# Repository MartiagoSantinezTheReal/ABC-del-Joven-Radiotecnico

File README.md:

# ABC-del-Joven-Radiotecnico
Este repositorio contendrá todos mis avances mientras leo el libro "ABC del Joven Radiotécnico" de Viktor Borísov, con el objetivo final de implementar la Radio Superheterodína que se muestra en el libro para el curso EL3202 "Circuitos Eléctricos Analógicos". Este repositorio posteriormente será utilizado para continuar adaptando el libro.

El objetivo primario de este repositorio, como se mencionó anteriormente, será el estudio del libro, particularmente desde la Charla 11 en adelante, sin embargo esto cambiará cuando termine el curso, ya que tengo la intención de hacer un análisis y adaptación del libro completo para que utilice componentes modernos (El libro fue escrito en los 80s en la Union Sovietica por lo que los componentes en los que se basan los circuitos son, al menos, dificiles de conseguir). 

Digo lo anterior ya que me saltaré partes del libro como la elaboración de fuentes de poder o condensadores variables ya que en el laboratorio tendré acceso a estas piezas (Como dije anteriormente es un tema al que volveré en un futuro). 

Tengo también la intención de traducir ediciones de la revista sovietica “Radio” ya que esta tiene una gran cantidad de información util para radioaficionados y sus circuitos deben pasar por un proceso similar al de los circuitos del libro para que puedan ser usados actualmente. Sin embargo esto será trabajo futuro y solo será si consigo permiso del dueño de la página de la cual estoy obteniendo las revistas para hacer este trabajo.

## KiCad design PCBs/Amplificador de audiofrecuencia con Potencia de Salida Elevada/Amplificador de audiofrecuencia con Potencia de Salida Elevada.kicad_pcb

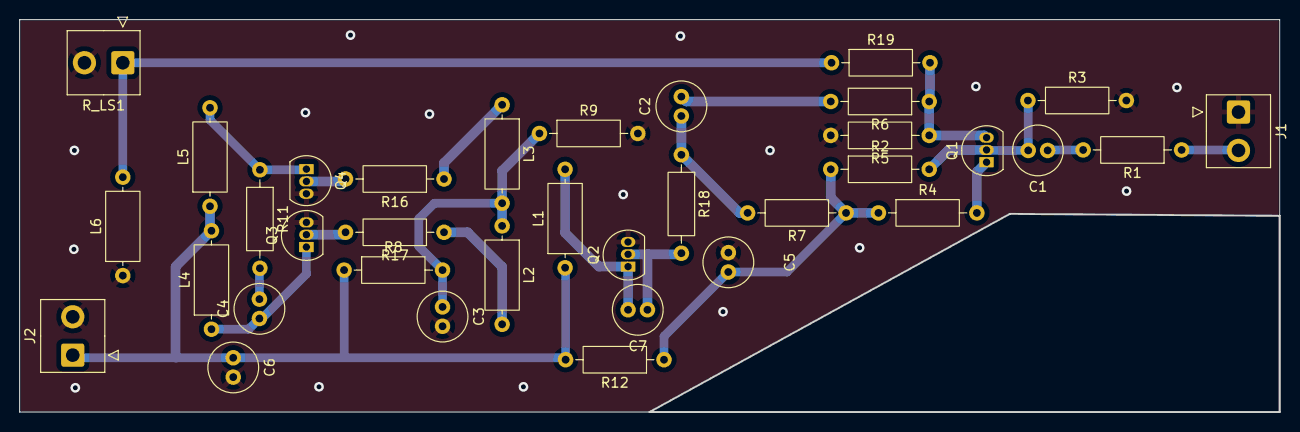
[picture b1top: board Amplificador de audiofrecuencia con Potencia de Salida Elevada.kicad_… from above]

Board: 2 copper layers, 130.0 x 40.4 mm, 35 parts (0 on the bottom side), 21 nets.

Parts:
C1: 1u; C_Radial_D5.0mm_H11.0mm_P2.00mm
C2: 10u; C_Radial_D5.0mm_H11.0mm_P2.00mm
C3: 100u; C_Radial_D5.0mm_H11.0mm_P2.00mm
C4: 0.01u; C_Radial_D5.0mm_H11.0mm_P2.00mm
C5: c=25u; C_Radial_D5.0mm_H11.0mm_P2.00mm
C6: 470u; C_Radial_D5.0mm_H11.0mm_P2.00mm
C7: 1n; C_Radial_D5.0mm_H11.0mm_P2.00mm
J1, J2: Conn_01x02_Socket; TE_826576-2_1x02_P3.96mm_Vertical
L1: 100m; L_Axial_L7.0mm_D3.3mm_P10.16mm_Horizontal_Fastron_MICC
L2, L3: 13.9m; L_Axial_L7.0mm_D3.3mm_P10.16mm_Horizontal_Fastron_MICC
L4, L5: 160m; L_Axial_L7.0mm_D3.3mm_P10.16mm_Horizontal_Fastron_MICC
L6: 10m; L_Axial_L7.0mm_D3.3mm_P10.16mm_Horizontal_Fastron_MICC
Q1, Q2: 2N3906; TO-92L_Inline
Q3, Q4: BC327-40; TO-92L_Inline
R1, R6, R12: r=1k; R_Axial_DIN0207_L6.3mm_D2.5mm_P10.16mm_Horizontal
R2: 820k; R_Axial_DIN0207_L6.3mm_D2.5mm_P10.16mm_Horizontal
R3: 1G; R_Axial_DIN0207_L6.3mm_D2.5mm_P10.16mm_Horizontal
R4, R5: 4.7k; R_Axial_DIN0207_L6.3mm_D2.5mm_P10.16mm_Horizontal
R7: 82k; R_Axial_DIN0207_L6.3mm_D2.5mm_P10.16mm_Horizontal
R8: 3.1k; R_Axial_DIN0207_L6.3mm_D2.5mm_P10.16mm_Horizontal
R9: 270; R_Axial_DIN0207_L6.3mm_D2.5mm_P10.16mm_Horizontal
R11, R16, R17: 100; R_Axial_DIN0207_L6.3mm_D2.5mm_P10.16mm_Horizontal
R18: 47; R_Axial_DIN0207_L6.3mm_D2.5mm_P10.16mm_Horizontal
R19: 22k; R_Axial_DIN0207_L6.3mm_D2.5mm_P10.16mm_Horizontal
R_LS1: 8; TE_826576-2_1x02_P3.96mm_Vertical

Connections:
0: C3.2, C5.1, C6.2, J1.1, J2.2, L6.1, Q2.3 (E), Q3.3 (E), Q4.3 (E), R3.2, R5.2, R9.2, R_LS1.2
IN: J1.2, R1.1
unnamed: C1.1, R1.2
unnamed: C2.1, R7.2, R18.1
unnamed: C2.2, R6.2
unnamed: C3.1, L2.1, L3.2, R8.2, R9.1
unnamed: C4.2, R11.2
unnamed: C5.2, R2.1, R4.1, R7.1, R12.1
unnamed: L2.2, R17.1
unnamed: L3.1, R16.1
unnamed: C1.2, Q1.2 (B), R2.2, R3.1
unnamed: Q1.1 (C), R4.2
unnamed: Q1.3 (E), R5.1, R6.1, R19.2
unnamed: C7.1, Q2.2 (B), R18.2
unnamed: C7.2, L1.2, Q2.1 (C)
unnamed: Q3.2 (B), R17.2
unnamed: C4.1, L4.1, Q3.1 (C)
unnamed: Q4.2 (B), R16.2
unnamed: L5.2, Q4.1 (C), R11.1
OUT: L6.2, R19.1, R_LS1.1
POWER: C6.1, J2.1, L1.1, L4.2, L5.1, R8.1, R12.2

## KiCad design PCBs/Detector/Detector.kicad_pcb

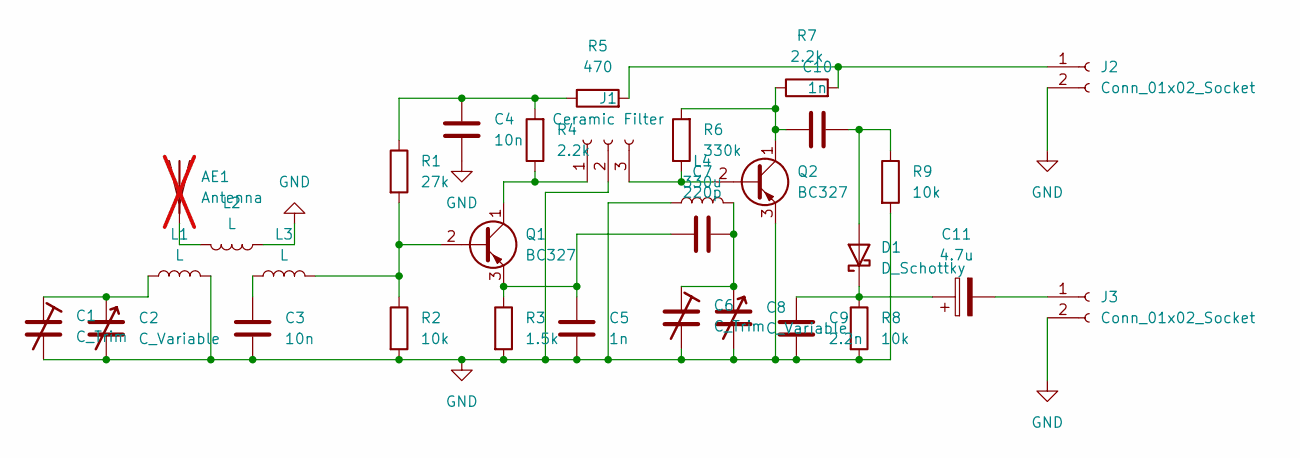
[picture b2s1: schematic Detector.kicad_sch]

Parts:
AE1: Antenna; not fitted
C1, C6: C_Trim; C_Disc_D6.0mm_W4.4mm_P5.00mm
C2, C8: C_Variable; TerminalBlock_Xinya_XY308-2.54-2P_1x02_P2.54mm_Horizontal
C3, C4: 10n; C_Radial_D6.3mm_H11.0mm_P2.50mm
C5, C10: 1n; C_Radial_D6.3mm_H11.0mm_P2.50mm
C7: 220p; C_Radial_D6.3mm_H11.0mm_P2.50mm
C9: 2.2n; C_Radial_D6.3mm_H11.0mm_P2.50mm
C11: 4.7u; C_Radial_D6.3mm_H11.0mm_P2.50mm
D1: D_Schottky; D_DO-34_SOD68_P7.62mm_Horizontal
J1: Ceramic Filter
J2, J3: Conn_01x02_Socket; TerminalBlock_Xinya_XY308-2.54-2P_1x02_P2.54mm_Horizontal
L1, L2, L3: L; L_Axial_L5.3mm_D2.2mm_P7.62mm_Horizontal_Vishay_IM-1
L4: 330u; L_Axial_L5.3mm_D2.2mm_P7.62mm_Horizontal_Vishay_IM-1
Q1, Q2: BC327; TO-92_Inline
R1: 27k; R_Axial_DIN0411_L9.9mm_D3.6mm_P12.70mm_Horizontal
R2, R8, R9: 10k; R_Axial_DIN0411_L9.9mm_D3.6mm_P12.70mm_Horizontal
R3: 1.5k; R_Axial_DIN0411_L9.9mm_D3.6mm_P12.70mm_Horizontal
R4, R7: 2.2k; R_Axial_DIN0411_L9.9mm_D3.6mm_P12.70mm_Horizontal
R5: 470; R_Axial_DIN0411_L9.9mm_D3.6mm_P12.70mm_Horizontal
R6: 330k; R_Axial_DIN0411_L9.9mm_D3.6mm_P12.70mm_Horizontal

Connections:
GND: C1.2, C2.2, C3.1, C4.1, C5.1, C6.2, C8.2, C9.2, J1.2, J2.2, J3.2, L1.2, L2.1, L4.1, Q2.3 (E), R2.2, R3.2, R8.2, R9.2
unnamed: C1.1, C2.1, L1.1
unnamed: C3.2, L3.1
unnamed: C4.2, R1.1, R4.2, R5.1
unnamed: C6.1, C7.2, C8.1, L4.2
unnamed: C10.2, D1.2 (A), R9.1
unnamed: C9.1, C11.1, D1.1 (K), R8.1
unnamed: J1.1, Q1.1 (C), R4.1
unnamed: J1.3, Q2.2 (B), R6.1
unnamed: J2.1, R5.2, R7.2
unnamed: C11.2, J3.1
unnamed: AE1.1, L2.2
unnamed: L3.2, Q1.2 (B), R1.2, R2.1
unnamed: C5.2, C7.1, Q1.3 (E), R3.1
unnamed: C10.1, Q2.1 (C), R6.2, R7.1

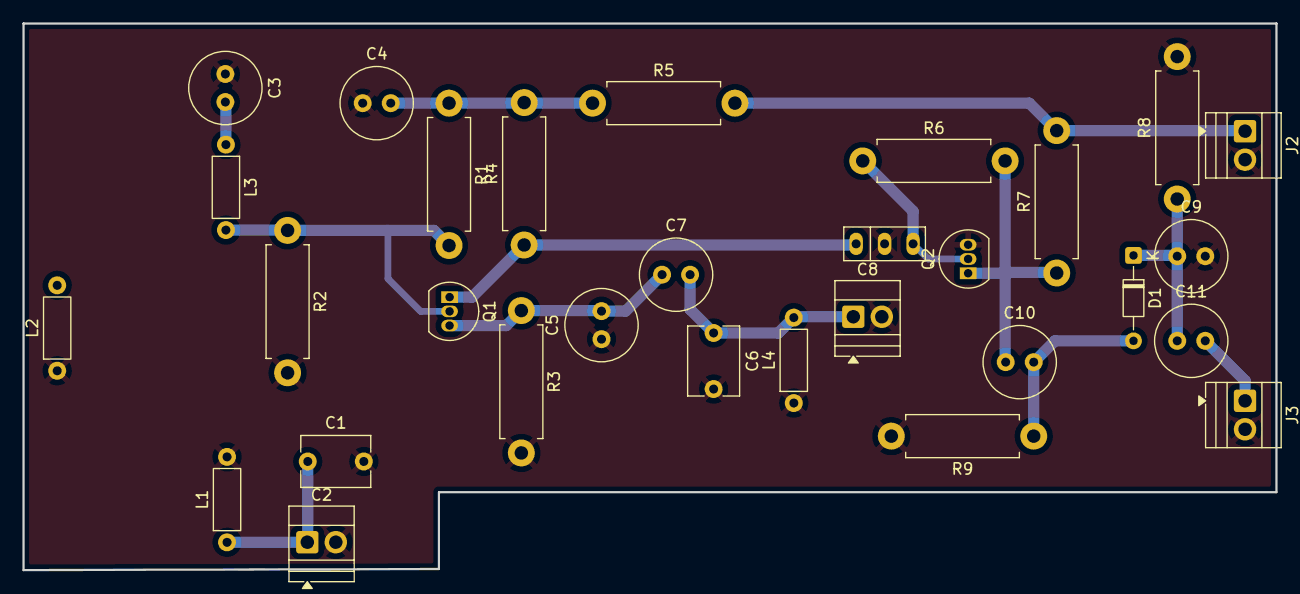
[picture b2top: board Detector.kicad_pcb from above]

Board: 2 copper layers, 111.8 x 48.8 mm, 30 parts (0 on the bottom side), 14 nets.

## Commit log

2026-03-20 Primer commit, añadiendo la estructura del repositorio
2026-03-20 Segundo commit, añadiendo la estructura del repositorio correctamente :p
2026-03-23 Se creó la primera versión del Amplificador Simple de Dos Etapas de la Charla 11, se añade una descripción de las modificaciones hechas al circuito y se reportan las futuras modificaciones del circui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
2026-03-23 Se hizo una revisión al circuito del amplificador simple, se logró hacer que funcione con transistores modernos 2N3906.
2026-03-24 Creacion del Amplificador de audiofrecuencia con POtencia de Salida Elevada (Experimento con bajo exito).
2026-05-28 Se creó una nueva version del Amplificador simple, siendo seleccionado como amplificador final, se creó el circuito del detector sin embargo no fue testeado por la dificultad de crear una simulación 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
